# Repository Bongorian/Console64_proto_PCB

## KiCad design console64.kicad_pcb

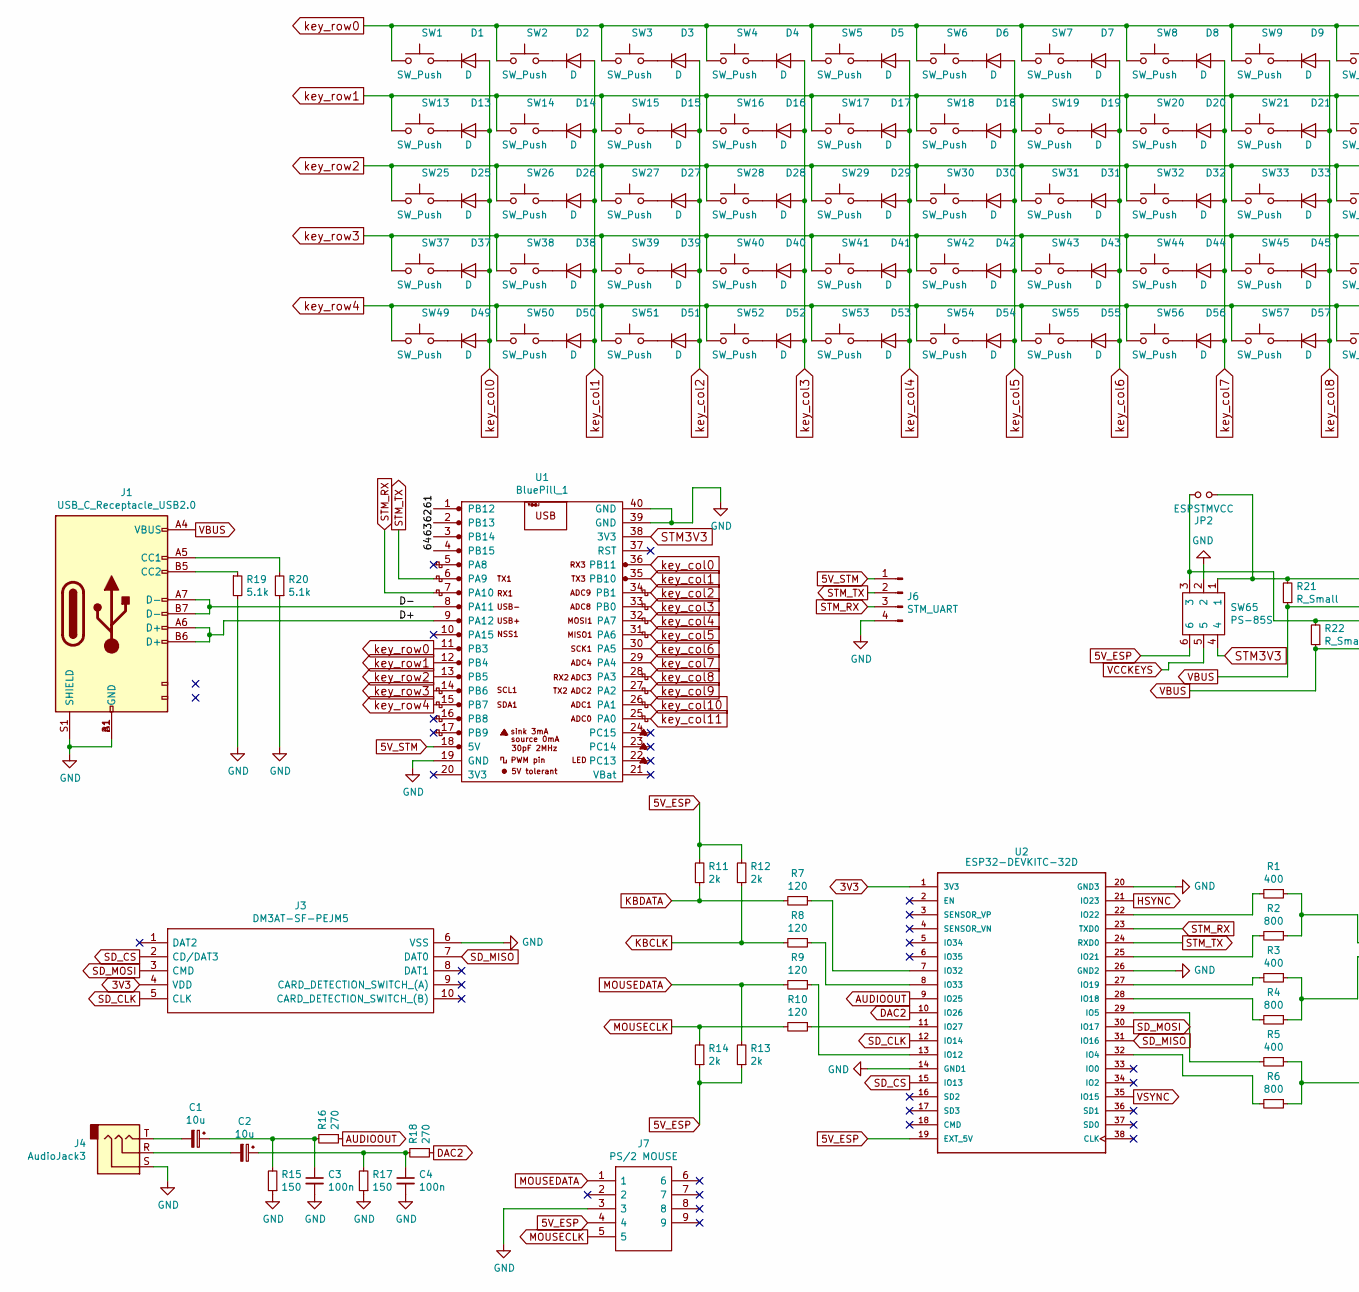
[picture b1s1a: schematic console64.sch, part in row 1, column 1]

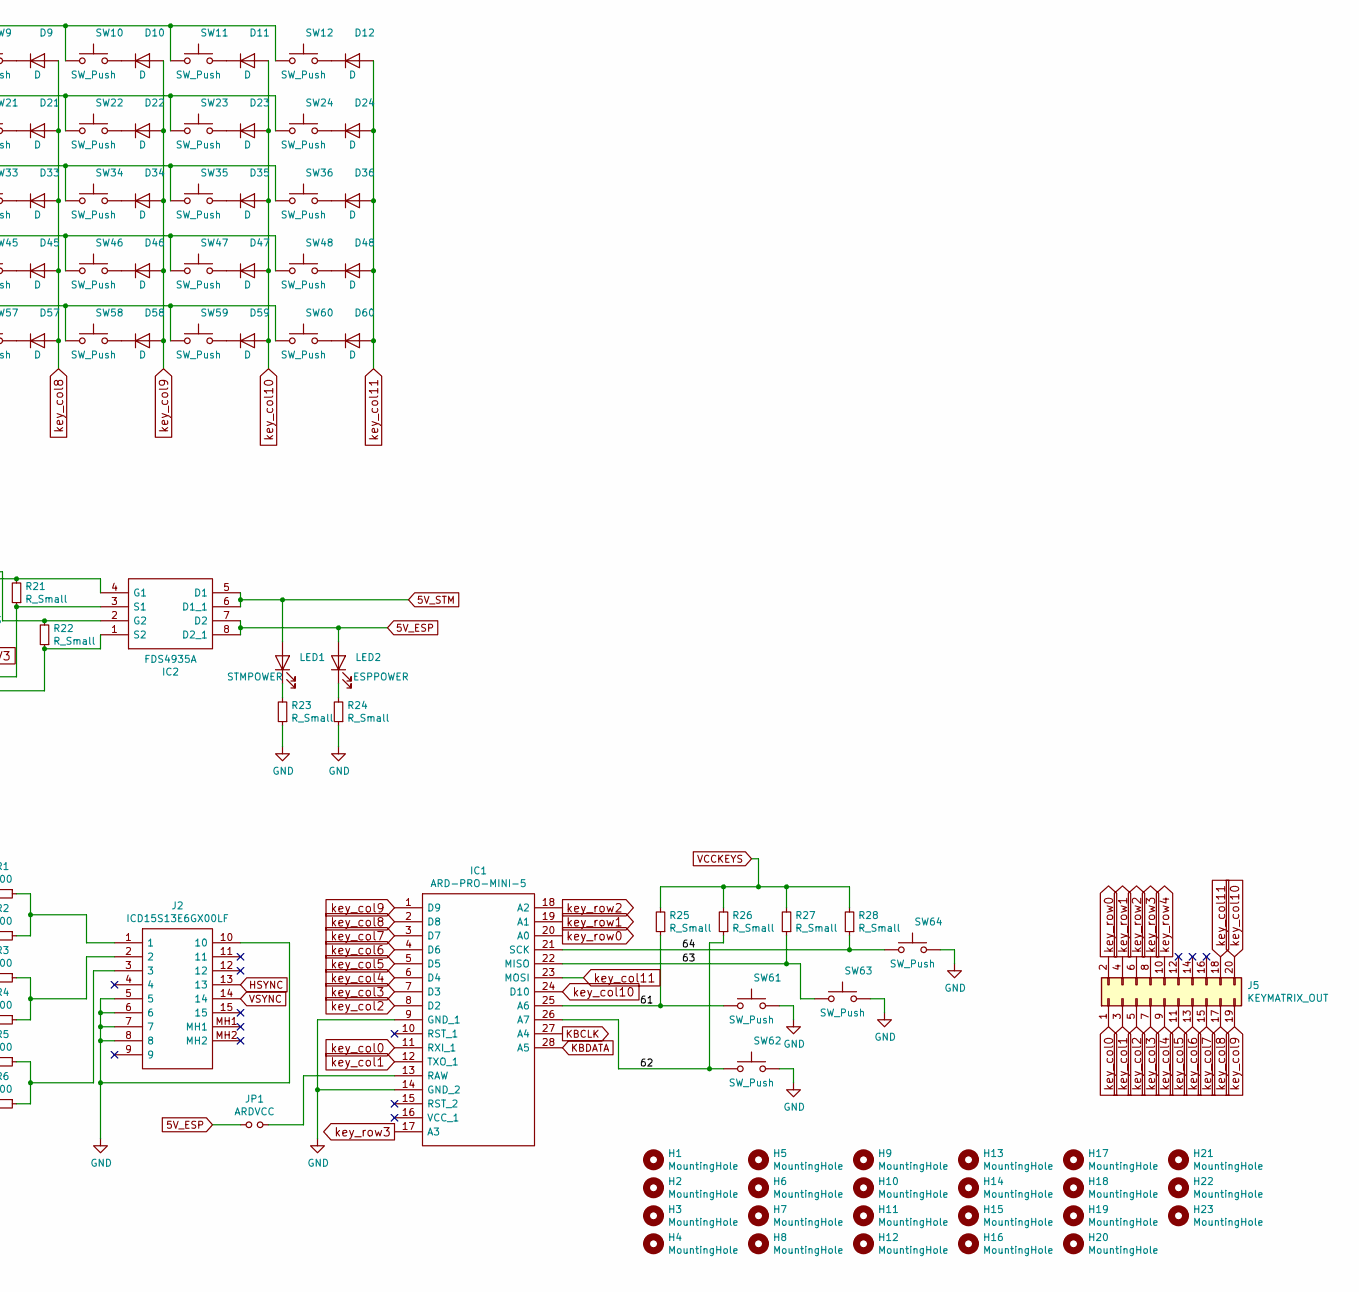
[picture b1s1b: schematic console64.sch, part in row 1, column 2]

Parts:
C1, C2: 10u; CP_Radial_D5.0mm_P2.00mm
C3, C4: 100n; C_Disc_D5.0mm_W2.5mm_P2.50mm
D1, D2, D3, D4, D5, D6, D7, D8, D9, D10, D11, D12, D13, D14, D15, D16, D17, D18, D19, D20, D21, D22, D23, D24, D25, D26, D27, D28, D29, D30, D31, D32, D33, D34, D35, D36, D37, D38, D39, D40, D41, D42, D43, D44, D45, D46, D47, D48, D49, D50, D51, D52, D53, D54, D55, D56, D57, D58, D59, D60: D; DIODE_KB
H1, H2, H3, H4, H5, H6, H7, H8, H9, H10, H11, H12, H13, H14, H15, H16, H17, H18, H19, H20, H21, H22, H23: MountingHole; MountingHole_2.2mm_M2
IC1: ARD-PRO-MINI-5; ARDPROMINI5_NOHEAD; Manufacturer_Part_Number ARD-PRO-MINI-5; Mouser Part Number 992-ARD-PRO-MINI-5
IC2: FDS4935A; Manufacturer_Part_Number FDS4935A; Mouser Part Number 512-FDS4935A
J1: USB_C_Receptacle_USB2.0; USB_C_Receptacle_Palconn_UTC16-G-NoSBU
J2: ICD15S13E6GX00LF; Manufacturer_Part_Number ICD15S13E6GX00LF; Mouser Part Number 649-ICD15S13E6GXLF
J3: DM3AT-SF-PEJM5; DM3AT-SF-PEJM5_1; Manufacturer_Part_Number DM3AT-SF-PEJM5; Mouser Part Number 798-DM3AT-SF-PEJM5
J4: AudioJack3; Jack_3.5mm_Switronic_ST-005-G_horizontal
J5: KEYMATRIX_OUT; PinHeader_2x10_P1.27mm_Vertical_SMD
J6: STM_UART; PinHeader_1x04_P2.54mm_Horizontal
J7: PS/2 MOUSE; 57492651; Manufacturer_Part_Number 5749265-1; Mouser Part Number 571-5749265-1
JP1: ARDVCC; PinHeader_1x02_P2.54mm_Vertical
JP2: ESPSTMVCC; PinHeader_1x02_P2.54mm_Vertical
LED1: STMPOWER; LED_D5.0mm_Clear
LED2: ESPPOWER; LED_D5.0mm_Clear
R1, R3, R5: 400; R_Axial_DIN0204_L3.6mm_D1.6mm_P7.62mm_Horizontal
R2, R4, R6: 800; R_Axial_DIN0204_L3.6mm_D1.6mm_P7.62mm_Horizontal
R7, R8, R9, R10: 120; R_Axial_DIN0204_L3.6mm_D1.6mm_P7.62mm_Horizontal
R11, R12, R13, R14: 2k; R_Axial_DIN0204_L3.6mm_D1.6mm_P7.62mm_Horizontal
R15, R17: 150; R_Axial_DIN0204_L3.6mm_D1.6mm_P7.62mm_Horizontal
R16, R18: 270; R_Axial_DIN0204_L3.6mm_D1.6mm_P7.62mm_Horizontal
R19, R20: 5.1k; R_Axial_DIN0204_L3.6mm_D1.6mm_P7.62mm_Horizontal
R21, R22, R23, R24, R25, R26, R27, R28: R_Small; R_Axial_DIN0204_L3.6mm_D1.6mm_P7.62mm_Horizontal
SW1, SW2, SW3, SW4, SW5, SW6, SW7, SW8, SW9, SW10, SW11, SW12, SW13, SW14, SW15, SW16, SW17, SW18, SW19, SW20, SW21, SW22, SW23, SW24, SW25, SW26, SW27, SW28, SW29, SW30, SW31, SW32, SW33, SW34, SW35, SW36, SW37, SW38, SW39, SW40, SW41, SW42, SW43, SW44, SW45, SW46, SW47, SW48, SW49, SW50, SW51, SW52, SW53, SW54, SW55, SW56, SW57, SW58, SW59, SW60, SW61, SW62, SW63, SW64: SW_Push; SW_PG1350_inname
SW65: PS-85S
U1: BluePill_1; BluePill_nosilks
U2: ESP32-DEVKITC-32D; MODULE_ESP32-DEVKITC-32D

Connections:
3V3: J3.4 (VDD), U2.1 (3V3)
5V_ESP: IC2.7 (D2), IC2.8 (D2_1), J7.4, JP1.1, LED2.2 (A), R11.2, R12.2, R13.1, R14.1, SW65.6, U2.19 (EXT_5V)
5V_STM: IC2.5 (D1), IC2.6 (D1_1), J6.1, LED1.2 (A), U1.18 (5V)
/61: IC1.25 (A6), R25.1, SW61.1, U1.1 (PB12)
/62: IC1.26 (A7), R26.1, SW62.1, U1.2 (PB13)
/63: IC1.22 (MISO), R27.1, SW63.1, U1.3 (PB14)
/64: IC1.21 (SCK), R28.1, SW64.1, U1.4 (PB15)
/D+: J1.A6 (D+), J1.B6 (D+), U1.9 (PA12)
/D-: J1.A7 (D-), J1.B7 (D-), U1.8 (PA11)
AUDIOOUT: R16.1, U2.9 (IO25)
DAC2: R18.1, U2.10 (IO26)
GND: C3.2, C4.2, IC1.9 (GND_1), IC1.14 (GND_2), J1.A1 (GND), J1.B1 (GND), J1.S1 (SHIELD), J2.5, J2.6, J2.7, J2.8, J2.10, J3.6 (VSS), J4.S, J6.4, J7.3, R15.1, R17.1, R19.2, R20.1, R23.1, R24.1, SW61.2, SW62.2, SW63.2, SW64.2, SW65.2, U1.19 (GND), U1.39 (GND), U1.40 (GND), U2.14 (GND1), U2.20 (GND3), U2.26 (GND2)
HSYNC: J2.13, U2.21 (IO23)
KBCLK: IC1.27 (A4), R8.2, R12.1
KBDATA: IC1.28 (A5), R7.2, R11.1
MOUSECLK: J7.5, R10.2, R14.2
MOUSEDATA: J7.1, R9.2, R13.2
unnamed: C1.1, C3.1, R15.2, R16.2
unnamed: C1.2, J4.T
unnamed: C2.1, C4.1, R17.2, R18.2
unnamed: C2.2, J4.R
unnamed: D1.1 (K), SW1.2
unnamed: D2.1 (K), SW2.2
unnamed: D3.1 (K), SW3.2
unnamed: D4.1 (K), SW4.2
unnamed: D5.1 (K), SW5.2
unnamed: D6.1 (K), SW6.2
unnamed: D7.1 (K), SW7.2
unnamed: D8.1 (K), SW8.2
unnamed: D9.1 (K), SW9.2
unnamed: D10.1 (K), SW10.2
unnamed: D11.1 (K), SW11.2
unnamed: D12.1 (K), SW12.2
unnamed: D13.1 (K), SW13.2
unnamed: D14.1 (K), SW14.2
unnamed: D15.1 (K), SW15.2
unnamed: D16.1 (K), SW16.2
unnamed: D17.1 (K), SW17.2
unnamed: D18.1 (K), SW18.2
unnamed: D19.1 (K), SW19.2
unnamed: D20.1 (K), SW20.2
unnamed: D21.1 (K), SW21.2
unnamed: D22.1 (K), SW22.2
unnamed: D23.1 (K), SW23.2
unnamed: D24.1 (K), SW24.2
unnamed: D25.1 (K), SW25.2
unnamed: D26.1 (K), SW26.2
unnamed: D27.1 (K), SW27.2
unnamed: D28.1 (K), SW28.2
unnamed: D29.1 (K), SW29.2
unnamed: D30.1 (K), SW30.2
unnamed: D31.1 (K), SW31.2
unnamed: D32.1 (K), SW32.2
unnamed: D33.1 (K), SW33.2
unnamed: D34.1 (K), SW34.2
unnamed: D35.1 (K), SW35.2
unnamed: D36.1 (K), SW36.2
unnamed: D37.1 (K), SW37.2
unnamed: D38.1 (K), SW38.2
unnamed: D39.1 (K), SW39.2
unnamed: D40.1 (K), SW40.2
unnamed: D41.1 (K), SW41.2
unnamed: D42.1 (K), SW42.2
unnamed: D43.1 (K), SW43.2
unnamed: D44.1 (K), SW44.2
unnamed: D45.1 (K), SW45.2
unnamed: D46.1 (K), SW46.2
unnamed: D47.1 (K), SW47.2
unnamed: D48.1 (K), SW48.2
unnamed: D49.1 (K), SW49.2
unnamed: D50.1 (K), SW50.2
unnamed: D51.1 (K), SW51.2
unnamed: D52.1 (K), SW52.2
unnamed: D53.1 (K), SW53.2
unnamed: D54.1 (K), SW54.2
unnamed: D55.1 (K), SW55.2
unnamed: D56.1 (K), SW56.2
unnamed: D57.1 (K), SW57.2
unnamed: D58.1 (K), SW58.2
unnamed: D59.1 (K), SW59.2
unnamed: D60.1 (K), SW60.2
unnamed: IC1.13 (RAW), JP1.2
unnamed: IC2.2 (G2), JP2.2, R22.2, SW65.3
unnamed: IC2.4 (G1), JP2.1, R21.2, SW65.1
unnamed: J1.A5 (CC1), R20.2
unnamed: J1.B5 (CC2), R19.1
unnamed: J2.1, R1.1, R2.1
unnamed: J2.2, R3.1, R4.1
unnamed: J2.3, R5.1, R6.1
unnamed: LED1.1 (K), R23.2
unnamed: LED2.1 (K), R24.2
unnamed: R1.2, U2.22 (IO22)
unnamed: R2.2, U2.25 (IO21)
unnamed: R3.2, U2.27 (IO19)
unnamed: R4.2, U2.28 (IO18)
unnamed: R5.2, U2.29 (IO5)
unnamed: R6.2, U2.32 (IO4)
unnamed: R7.1, U2.7 (IO32)
unnamed: R8.1, U2.8 (IO33)
unnamed: R9.1, U2.13 (IO12)
unnamed: R10.1, U2.11 (IO27)
SD_CLK: J3.5 (CLK), U2.12 (IO14)
SD_CS: J3.2 (CD/DAT3), U2.15 (IO13)
SD_MISO: J3.7 (DAT0), U2.31 (IO16)
SD_MOSI: J3.3 (CMD), U2.30 (IO17)
STM3V3: SW65.4, U1.38 (3V3)
STM_RX: J6.3, U1.7 (PA10), U2.23 (TXD0)
STM_TX: J6.2, U1.6 (PA9), U2.24 (RXD0)
VBUS: IC2.1 (S2), IC2.3 (S1), J1.A4 (VBUS), J1.B4 (VBUS), R21.1, R22.1
VCCKEYS: R25.2, R26.2, R27.2, R28.2, SW65.5
VSYNC: J2.14, U2.35 (IO15)
key_col0: D1.2 (A), D13.2 (A), D25.2 (A), D37.2 (A), D49.2 (A), IC1.11 (RXI_1), J5.1, U1.36 (PB11)
key_col1: D2.2 (A), D14.2 (A), D26.2 (A), D38.2 (A), D50.2 (A), IC1.12 (TXO_1), J5.3, U1.35 (PB10)
key_col2: D3.2 (A), D15.2 (A), D27.2 (A), D39.2 (A), D51.2 (A), IC1.8 (D2), J5.5, U1.34 (PB1)
key_col3: D4.2 (A), D16.2 (A), D28.2 (A), D40.2 (A), D52.2 (A), IC1.7 (D3), J5.7, U1.33 (PB0)
key_col4: D5.2 (A), D17.2 (A), D29.2 (A), D41.2 (A), D53.2 (A), IC1.6 (D4), J5.9, U1.32 (PA7)
key_col5: D6.2 (A), D18.2 (A), D30.2 (A), D42.2 (A), D54.2 (A), IC1.5 (D5), J5.11, U1.31 (PA6)
key_col6: D7.2 (A), D19.2 (A), D31.2 (A), D43.2 (A), D55.2 (A), IC1.4 (D6), J5.13, U1.30 (PA5)
key_col7: D8.2 (A), D20.2 (A), D32.2 (A), D44.2 (A), D56.2 (A), IC1.3 (D7), J5.15, U1.29 (PA4)
key_col8: D9.2 (A), D21.2 (A), D33.2 (A), D45.2 (A), D57.2 (A), IC1.2 (D8), J5.17, U1.28 (PA3)
key_col9: D10.2 (A), D22.2 (A), D34.2 (A), D46.2 (A), D58.2 (A), IC1.1 (D9), J5.19, U1.27 (PA2)
key_col10: D11.2 (A), D23.2 (A), D35.2 (A), D47.2 (A), D59.2 (A), IC1.24 (D10), J5.20, U1.26 (PA1)
key_col11: D12.2 (A), D24.2 (A), D36.2 (A), D48.2 (A), D60.2 (A), IC1.23 (MOSI), J5.18, U1.25 (PA0)
key_row0: IC1.20 (A0), J5.2, SW1.1, SW2.1, SW3.1, SW4.1, SW5.1, SW6.1, SW7.1, SW8.1, SW9.1, SW10.1, SW11.1, SW12.1, U1.11 (PB3)
key_row1: IC1.19 (A1), J5.4, SW13.1, SW14.1, SW15.1, SW16.1, SW17.1, SW18.1, SW19.1, SW20.1, SW21.1, SW22.1, SW23.1, SW24.1, U1.12 (PB4)
key_row2: IC1.18 (A2), J5.6, SW25.1, SW26.1, SW27.1, SW28.1, SW29.1, SW30.1, SW31.1, SW32.1, SW33.1, SW34.1, SW35.1, SW36.1, U1.13 (PB5)
key_row3: IC1.17 (A3), J5.8, SW37.1, SW38.1, SW39.1, SW40.1, SW41.1, SW42.1, SW43.1, SW44.1, SW45.1, SW46.1, SW47.1, SW48.1, U1.14 (PB6)
key_row4: J5.10, SW49.1, SW50.1, SW51.1, SW52.1, SW53.1, SW54.1, SW55.1, SW56.1, SW57.1, SW58.1, SW59.1, SW60.1, U1.15 (PB7)

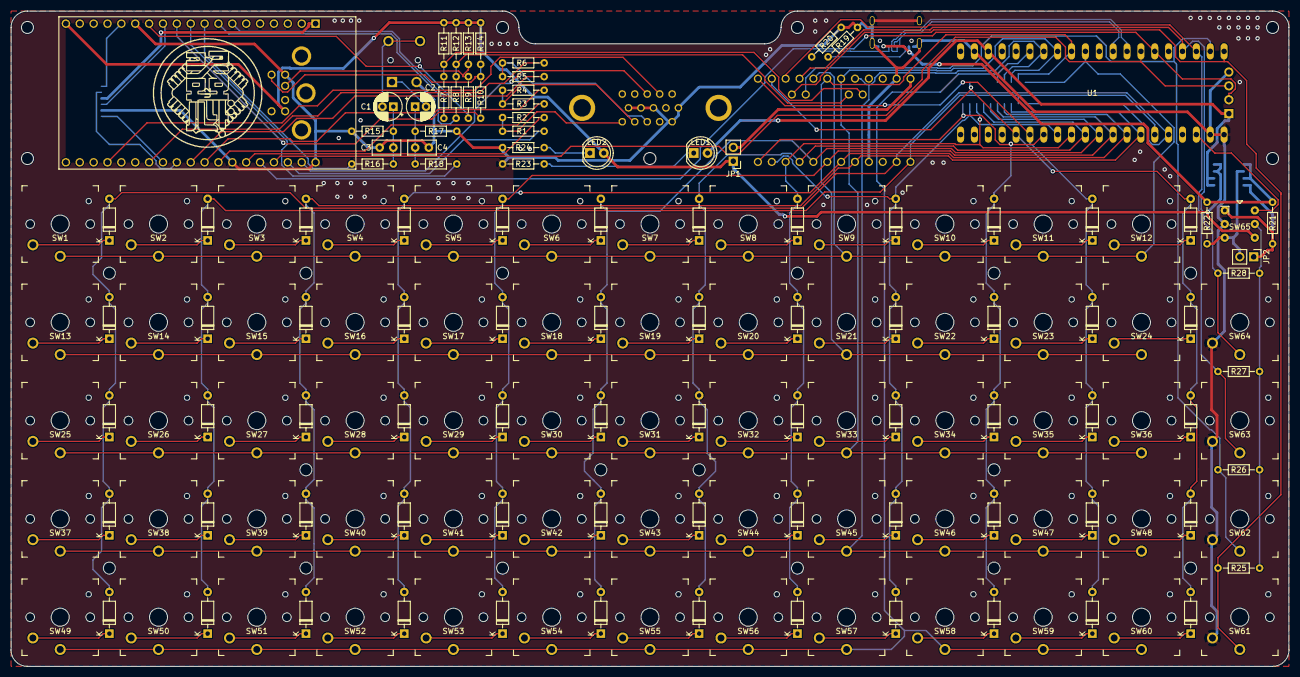
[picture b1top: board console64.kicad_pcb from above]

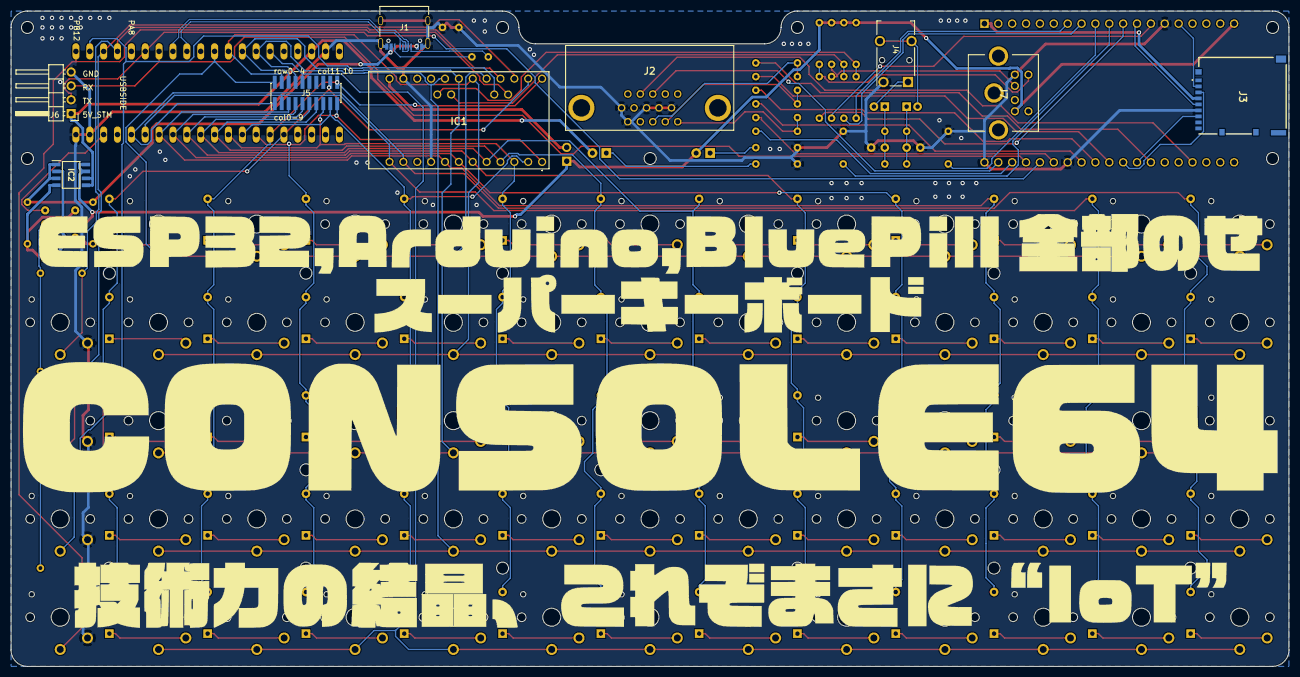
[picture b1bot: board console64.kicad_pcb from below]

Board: 2 copper layers, 234.0 x 120.0 mm, 195 parts (9 on the bottom side), 128 nets.

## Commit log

2020-03-07 routed
2020-03-10 production
